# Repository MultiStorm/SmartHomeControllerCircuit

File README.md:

# SmartHomeControllerCircuit
Wiring diagrams, PCB layouts for the Smart Home Controller.

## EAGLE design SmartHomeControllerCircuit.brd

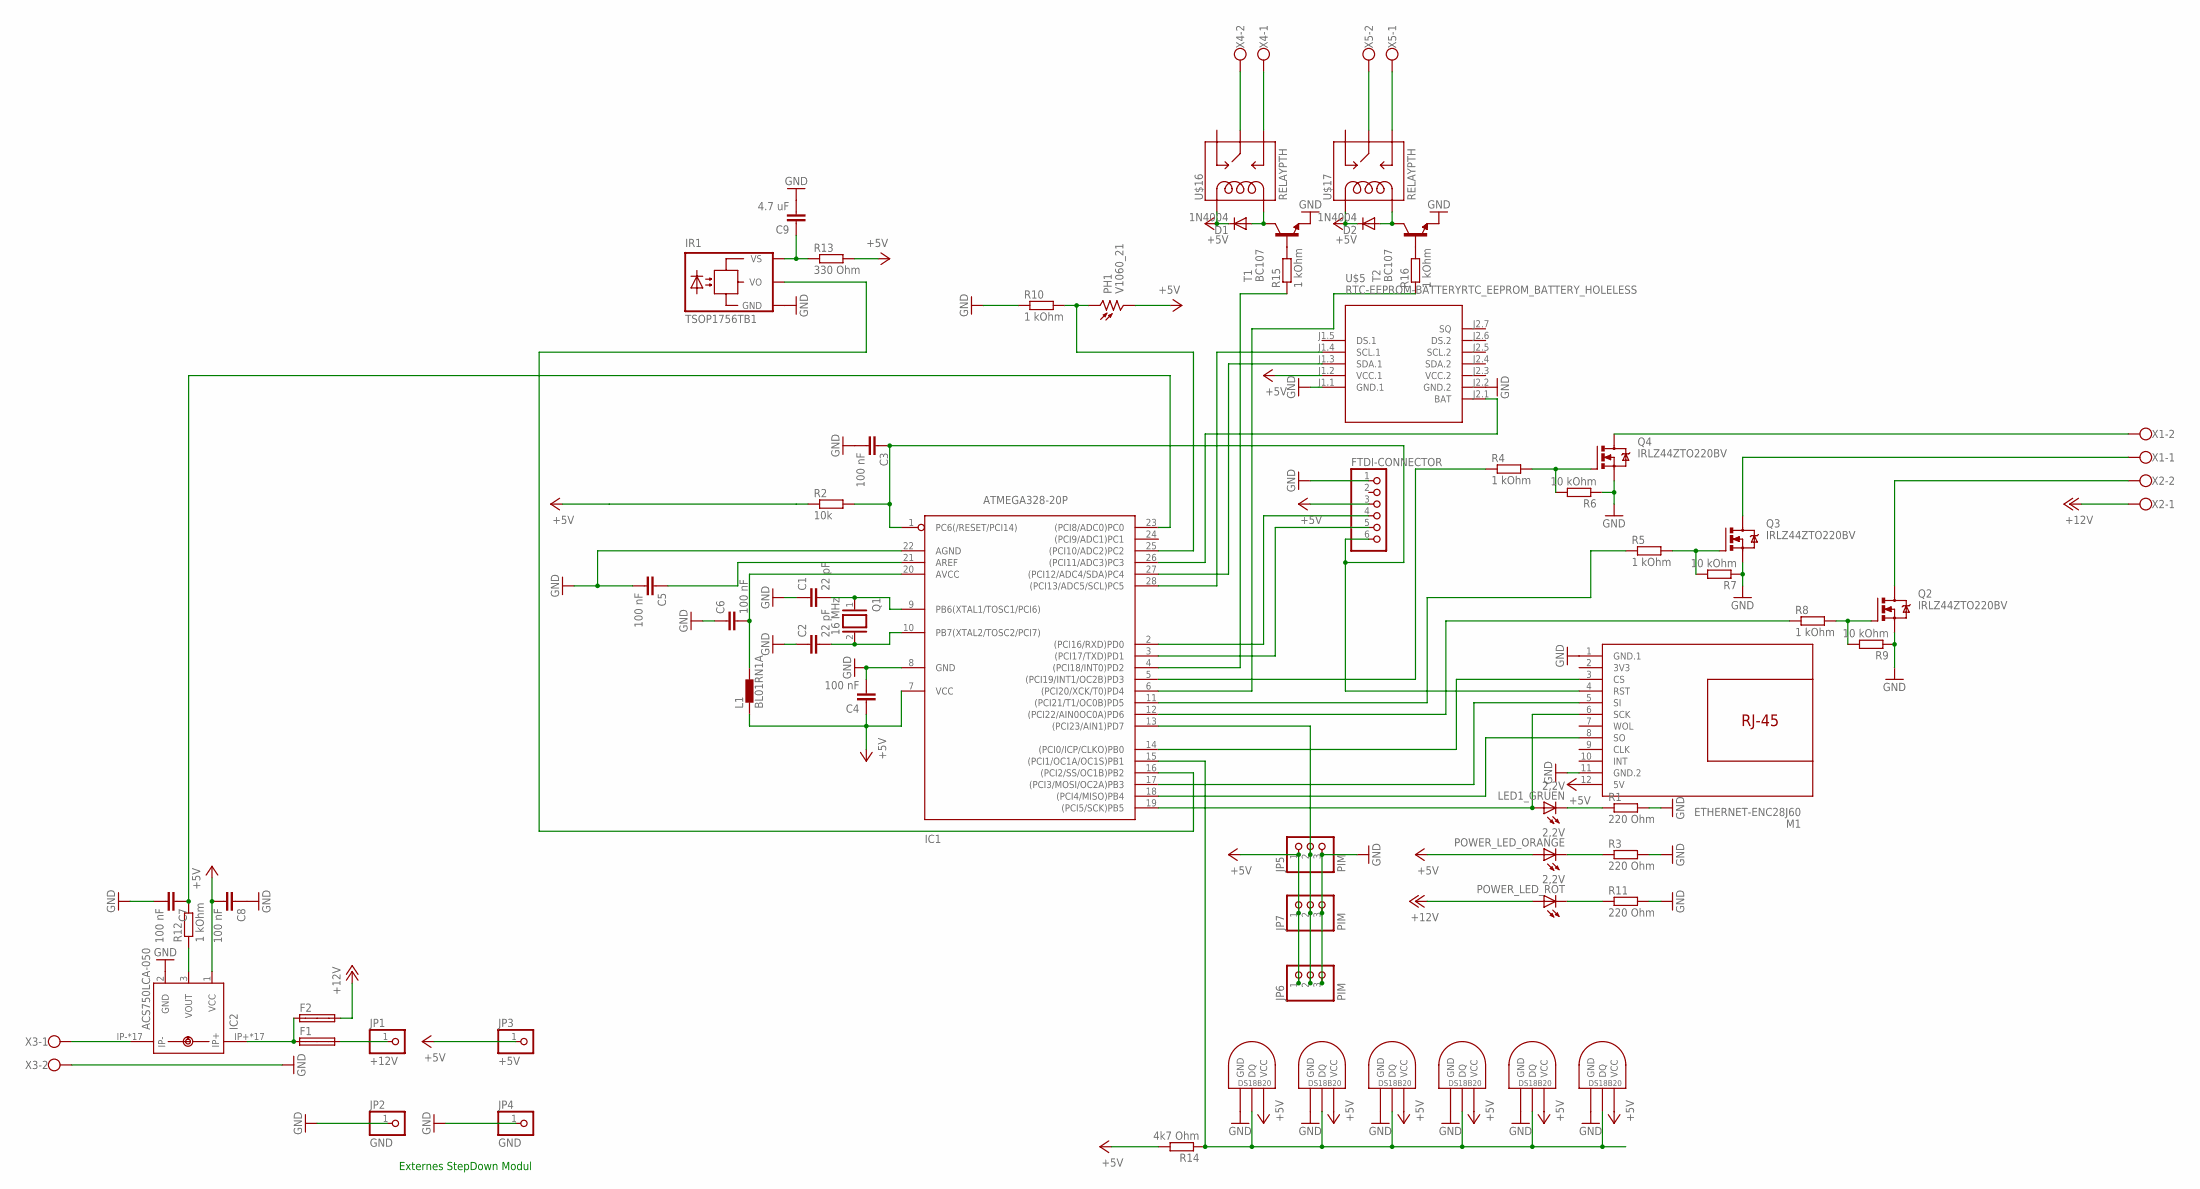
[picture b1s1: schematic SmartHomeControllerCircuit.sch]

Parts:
C1, C2: 22 pF; C050-024X044
C3, C4, C5, C6, C7, C8: 100 nF; C050-024X044
C9: 4.7 uF; C050-024X044
D1, D2: 1N4004; DO41-10
F1, F2: SH32
FTDI-CONNECTOR: 1X06
IC1: ATMEGA328-20P; DIL28-3
IC2: ACS750LCA-050; ACS75050
IR1: TSOP1756TB1; TSOP17_TB1
JP1: +12V; 1X01
JP2, JP4: GND; 1X01
JP3: +5V; 1X01
JP5, JP6, JP7: PIM; 1X03
L1: BL01RN1A
LED1_GRUEN: 2,2V; LED5MM
M1: ETHERNET-ENC28J60
PH1: V1060_21; TO-5_V10
POWER_LED_ORANGE: 2,2V; LED5MM
POWER_LED_ROT: 2,2V; LED5MM
Q1: 16 MHz; QS
Q2, Q3, Q4: IRLZ44ZTO220BV; TO220BV
R1, R3, R11: 220 Ohm; 0204/7
R2: 10k; 0204/7
R4, R5, R8, R10, R15, R16: 1 kOhm; 0309/12
R6, R7, R9: 10 kOhm; 0309/12
R12: 1 kOhm; 0204/7
R13: 330 Ohm; 0309/12
R14: 4k7 Ohm; 0204/7
T1, T2: BC107; TO18
U$5: RTC-EEPROM-BATTERYRTC_EEPROM_BATTERY_HOLELESS; RTC_EEPROM_BATTERY
U$10, U$11, U$12, U$13, U$14, U$15: DS1820TO92; DS1820
U$16, U$17: RELAYPTH; SRD-05VDC-SL-C
X1, X2, X3, X4, X5: W237-102

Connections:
3V3: M1.2 (3V3)
+5V: C4.1, C8.2, D1.C, D2.C, FTDI-CONNECTOR.3, IC1.7 (VCC), IC2.1 (VCC), JP3.1, JP5.1, JP6.1, JP7.1, L1.1, M1.12 (5V), PH1.2, POWER_LED_ORANGE.A, R2.1, R13.2, R14.2, U$5.J1.2 (VCC.1), U$10.VDD (VCC), U$11.VDD (VCC), U$12.VDD (VCC), U$13.VDD (VCC), U$14.VDD (VCC), U$15.VDD (VCC), U$16.COIL1, U$17.COIL1
+12V: F2.2A, POWER_LED_ROT.A, X2.1
+12V_IN: F1.1A, F2.1A, IC2.IP+, IC2.IP+@2 (IP+), IC2.IP+@3 (IP+), IC2.IP+@4 (IP+), IC2.IP+@5 (IP+), IC2.IP+@6 (IP+), IC2.IP+@7 (IP+), IC2.IP+@8 (IP+), IC2.IP+@9 (IP+), IC2.IP+@10 (IP+), IC2.IP+@11 (IP+), IC2.IP+@12 (IP+), IC2.IP+@13 (IP+), IC2.IP+@14 (IP+), IC2.IP+@15 (IP+), IC2.IP+@16 (IP+), IC2.IP+@17 (IP+), IC2.IP-, IC2.IP-@2 (IP-), IC2.IP-@3 (IP-), IC2.IP-@4 (IP-), IC2.IP-@5 (IP-), IC2.IP-@6 (IP-), IC2.IP-@7 (IP-), IC2.IP-@8 (IP-), IC2.IP-@9 (IP-), IC2.IP-@10 (IP-), IC2.IP-@11 (IP-), IC2.IP-@12 (IP-), IC2.IP-@13 (IP-), IC2.IP-@14 (IP-), IC2.IP-@15 (IP-), IC2.IP-@16 (IP-), IC2.IP-@17 (IP-), X3.1
GND: C1.1, C2.1, C3.2, C4.2, C5.2, C6.1, C7.2, C8.1, C9.2, FTDI-CONNECTOR.1, IC1.8 (GND), IC1.22 (AGND), IC2.2 (GND), IR1.GND, JP2.1, JP4.1, JP5.3, JP6.3, JP7.3, M1.1 (GND.1), M1.11 (GND.2), Q2.S, Q3.S, Q4.S, R1.2, R3.2, R6.1, R7.1, R9.1, R10.1, R11.2, T1.1 (E), T2.1 (E), U$5.J1.1 (GND.1), U$5.J2.2 (GND.2), U$10.GND, U$11.GND, U$12.GND, U$13.GND, U$14.GND, U$15.GND, X3.2
unnamed: C2.2, IC1.10 (PB7(XTAL2/TOSC2/PCI7)), Q1.2
unnamed: C1.2, IC1.9 (PB6(XTAL1/TOSC1/PCI6)), Q1.1
unnamed: C3.1, FTDI-CONNECTOR.6, IC1.1 (PC6(/RESET/PCI14)), M1.4 (RST), R2.2
unnamed: FTDI-CONNECTOR.4, IC1.2 ((PCI16/RXD)PD0)
unnamed: FTDI-CONNECTOR.5, IC1.3 ((PCI17/TXD)PD1)
unnamed: IC1.19 ((PCI5/SCK)PB5), LED1_GRUEN.A, M1.6 (SCK)
unnamed: LED1_GRUEN.K (C), R1.1
unnamed: POWER_LED_ORANGE.K (C), R3.1
unnamed: F1.2A, JP1.1
unnamed: IC1.25 ((PCI10/ADC2)PC2), PH1.1, R10.2
unnamed: C9.1, IR1.VS, R13.1
unnamed: IC1.28 ((PCI13/ADC5/SCL)PC5), U$5.J1.4 (SCL.1)
unnamed: IC1.27 ((PCI12/ADC4/SDA)PC4), U$5.J1.3 (SDA.1)
unnamed: IC1.14 ((PCI0/ICP/CLKO)PB0), M1.3 (CS)
unnamed: IC1.18 ((PCI4/MISO)PB4), M1.8 (SO)
unnamed: IC1.17 ((PCI3/MOSI/OC2A)PB3), M1.5 (SI)
unnamed: Q2.D, X2.2
unnamed: Q2.G, R8.2, R9.2
unnamed: Q3.D, X1.1
unnamed: Q4.D, X1.2
unnamed: Q3.G, R5.2, R7.2
unnamed: Q4.G, R4.2, R6.2
unnamed: IC1.5 ((PCI19/INT1/OC2B)PD3), R4.1
unnamed: IC1.11 ((PCI21/T1/OC0B)PD5), R5.1
unnamed: IC1.15 ((PCI1/OC1A/OC1S)PB1), R14.1, U$10.DQ, U$11.DQ, U$12.DQ, U$13.DQ, U$14.DQ, U$15.DQ
unnamed: C7.1, IC1.23 ((PCI8/ADC0)PC0), R12.2
unnamed: IC1.13 ((PCI23/AIN1)PD7), JP5.2, JP6.2, JP7.2
unnamed: POWER_LED_ROT.K (C), R11.1
unnamed: IC2.3 (VOUT), R12.1
unnamed: IC1.16 ((PCI2/SS/OC1B)PB2), IR1.VO
unnamed: IC1.12 ((PCI22/AIN0OC0A)PD6), R8.1
unnamed: U$16.SWCOMMON, X4.2
unnamed: IC1.26 ((PCI11/ADC3)PC3), U$5.J2.1 (BAT)
unnamed: U$16.SWOPEN, X4.1
unnamed: U$17.SWCOMMON, X5.2
unnamed: U$17.SWOPEN, X5.1
unnamed: IC1.4 ((PCI18/INT0)PD2), R15.1
unnamed: IC1.6 ((PCI20/XCK/T0)PD4), R16.1
unnamed: D1.A, T1.3 (C), U$16.COIL0
unnamed: D2.A, T2.3 (C), U$17.COIL0
unnamed: R15.2, T1.2 (B)
unnamed: R16.2, T2.2 (B)
unnamed: C5.1, IC1.21 (AREF)
unnamed: C6.2, IC1.20 (AVCC), L1.2
VCC.2: U$5.J2.3 (VCC.2)

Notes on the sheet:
Externes StepDown Modul

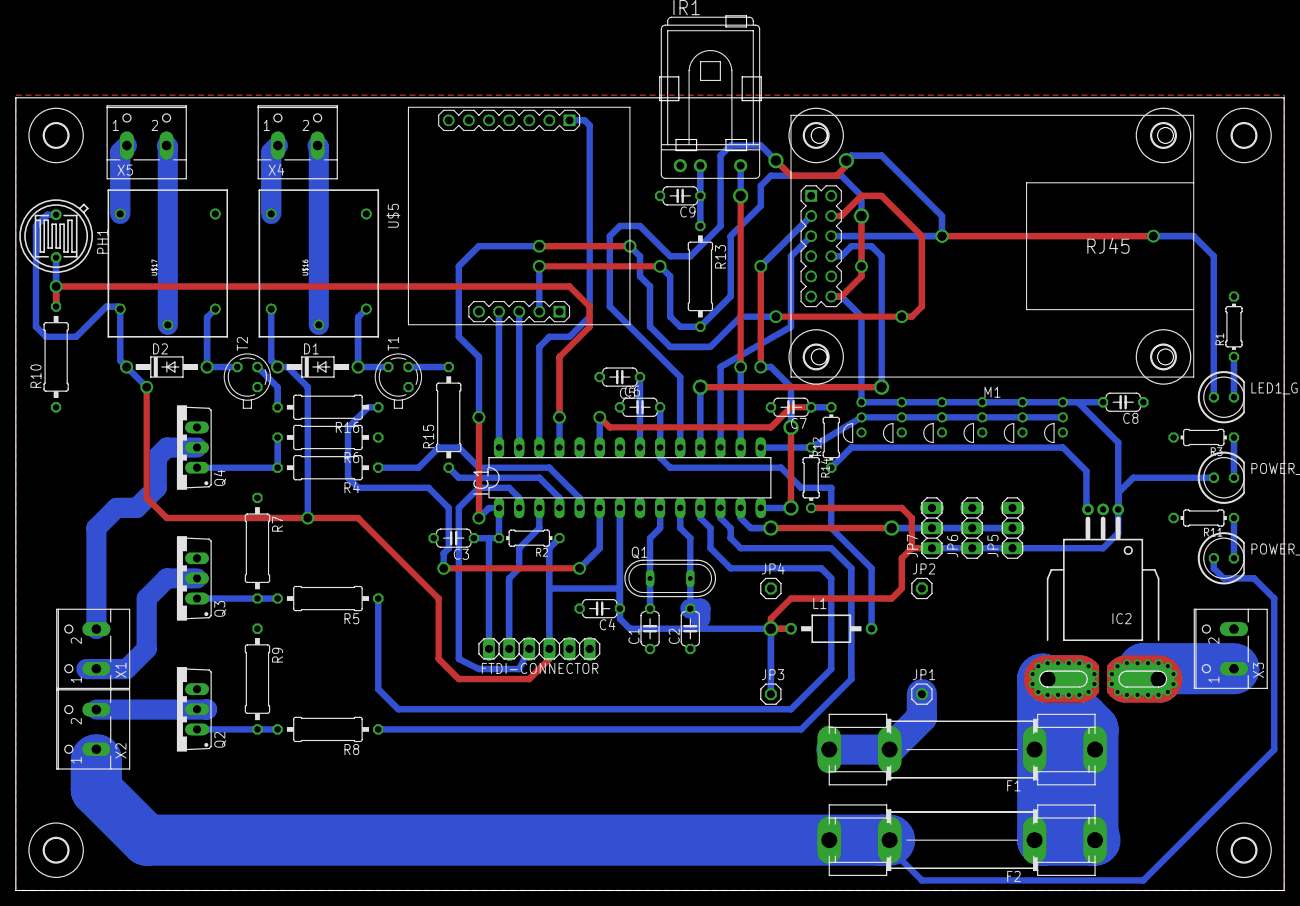
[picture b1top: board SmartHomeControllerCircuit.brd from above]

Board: 2 copper layers, 160.0 x 100.0 mm, 74 parts (0 on the bottom side), 48 nets.

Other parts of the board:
U$1, U$2, U$3, U$4, U$6, U$7, U$8, U$9: 3,0

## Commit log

2016-11-22 Init. This is the first version of the SmartHome Controller. The circuit has not yet been tested.

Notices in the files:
parts and their libraries:
diy-modules: Released under the Creative Commons Attribution 4.0 International License: http://creativecommons.org/licenses/by/4.0
